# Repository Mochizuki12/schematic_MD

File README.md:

# schematic_MD
### 2chモータドライバのプロトタイプ<br>
[回路の仕様](https://github.com/Mochizuki12/schematic_MD/blob/v0.1.0/documents/MDdocument.pdf)<br>
[回路図](https://github.com/Mochizuki12/schematic_MD/blob/v0.1.0/documents/MD_schematics.pdf)<br>
[PCB](https://github.com/Mochizuki12/schematic_MD/blob/v0.1.0/documents/pcb.pdf)<br>

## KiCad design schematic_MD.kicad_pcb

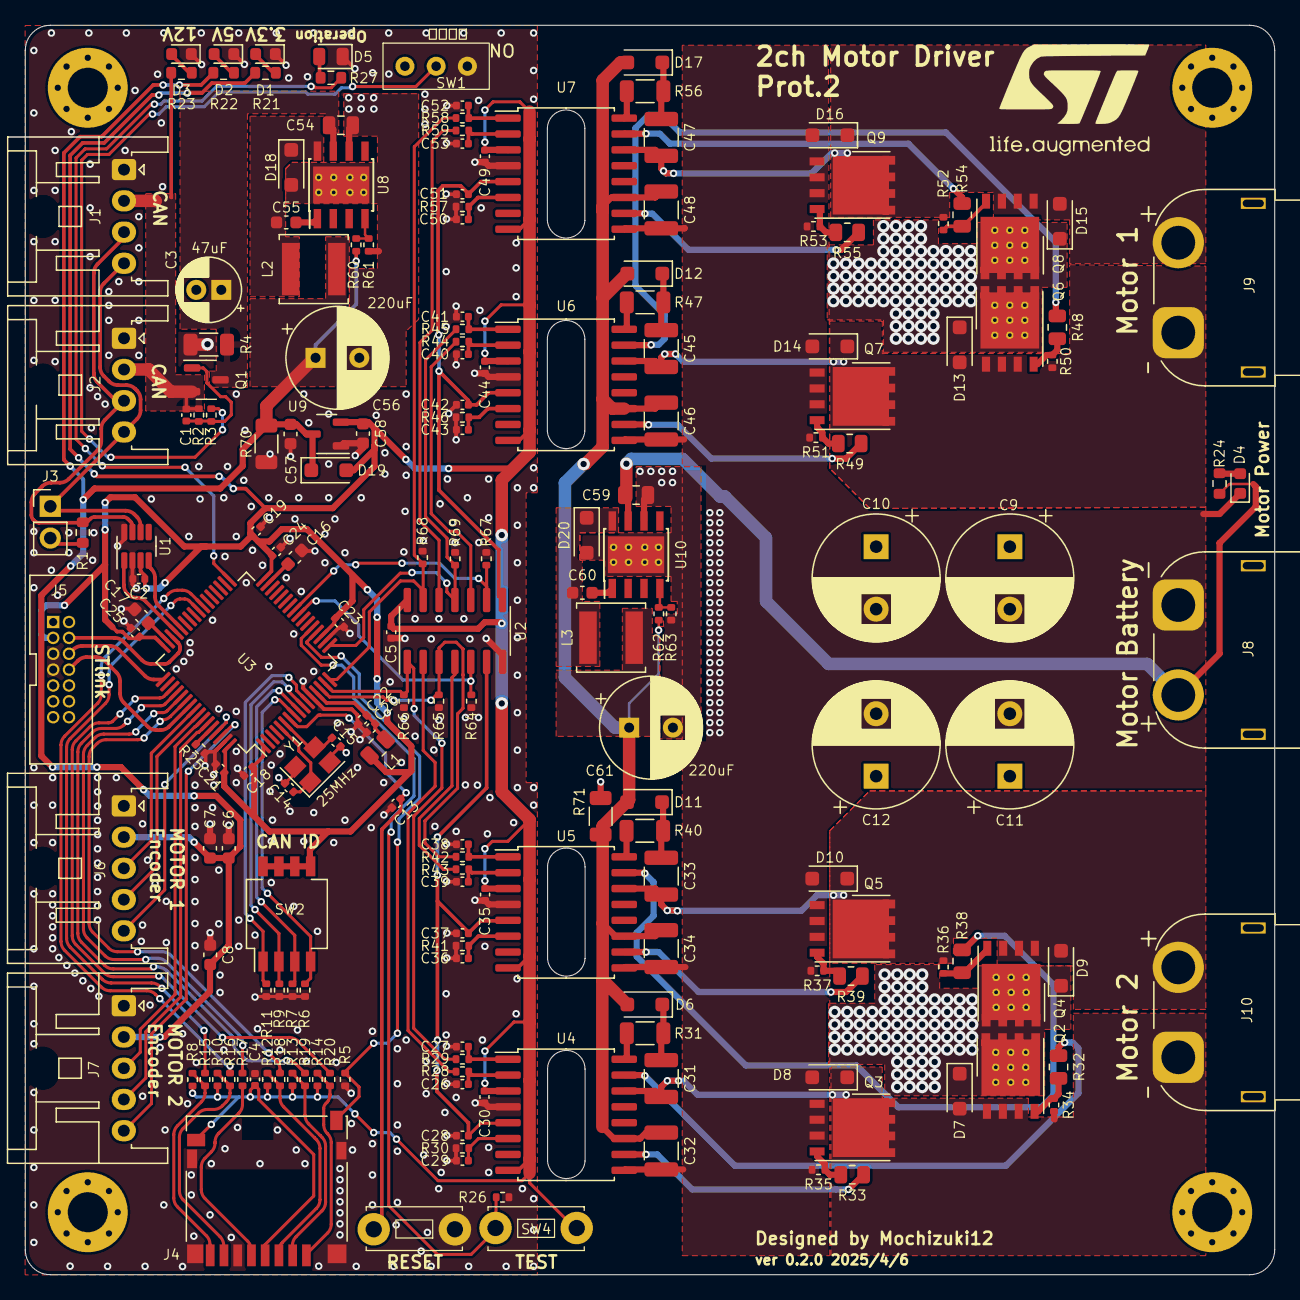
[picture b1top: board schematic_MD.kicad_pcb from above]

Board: 2 copper layers, 100.0 x 100.0 mm, 193 parts (0 on the bottom side), 113 nets.

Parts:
C1, C2, C4, C5, C13, C18, C21, C22, C23, C24, C25, C28, C29, C30, C35, C36, C37, C42, C43, C44, C49, C50, C51: 0.1uF; C_0402_1005Metric
C3: 47uF; CP_Radial_D5.0mm_P2.00mm
C6, C57, C58: 1uF; C_0603_1608Metric
C7, C8: 0.1uF; C_0603_1608Metric
C9, C10, C11, C12: 330uF; CP_Radial_D10.0mm_P5.00mm
C14, C15: 18pF; C_0402_1005Metric
C16, C17: 2.2uF; C_0603_1608Metric
C19: 4.7uF; C_0402_1005Metric
C20: 1uF; C_0402_1005Metric
C26, C27, C38, C39, C40, C41, C52, C53: 33pF; C_0402_1005Metric
C31, C32, C33, C34, C45, C46, C47, C48: 10uF; C_1210_3225Metric
C54, C59: 10uF; C_0805_2012Metric
C55, C60: 0.01uF; C_0603_1608Metric
C56, C61: 220uF; CP_Radial_D8.0mm_P3.50mm
D1, D2, D3, D4: LED; LED_0603_1608Metric
D5: LED; LED_0805_2012Metric
D6, D7, D8, D9, D10, D11, D12, D13, D14, D15, D16, D17, D18, D19, D20: D_Schottky; D_SOD-123F
H1, H2, H3, H4: MountingHole_Pad; MountingHole_3.2mm_M3_Pad_Via
J1, J2: CAN_Bus; JST_XA_S04B-XASK-1_1x04_P2.50mm_Horizontal
J3: Conn_02x01; PinHeader_1x02_P2.54mm_Vertical
J4: Micro_SD_Card_Det_Hirose_DM3AT; microSD_HC_Hirose_DM3D-SF
J5: Conn_02x07_Odd_Even; JTAG_box_connector
J6: Rotaly_encoder_1; JST_XA_S05B-XASK-1_1x05_P2.50mm_Horizontal
J7: Rotaly_encoder_2; JST_XA_S05B-XASK-1_1x05_P2.50mm_Horizontal
J8: XT60; AMASS_XT60PW-M_1x02_P7.20mm_Horizontal
J9, J10: XT60; AMASS_XT60PW-F_1x02_P7.20mm_Horizontal
L1: 600@100MHz; R_0805_2012Metric
L2, L3: 15uH; L_Sunlord_SWPA5040S
Q1: Q_PMOS_GSD; SOT-23-3
Q2, Q4, Q6, Q8: SQJ886EP-T1_GE3; Infineon_PG-TDSON-8_6.15x5.15mm_thermalvia
Q3, Q5, Q7, Q9: SQJ886EP-T1_GE3; Infineon_PG-TDSON-8_6.15x5.15mm
R1: 120; R_0603_1608Metric
R2, R3, R5, R6, R7, R8, R9, R10, R11, R12, R13, R14, R25, R26, R64, R65, R66, R67, R68, R69: 10k; R_0402_1005Metric
R4, R70, R71: 10k; R_1206_3216Metric
R15, R16, R17, R18, R19, R20: 0; R_0402_1005Metric
R21, R27: 330; R_0603_1608Metric
R22: 680; R_0603_1608Metric
R23: 2k; R_0603_1608Metric
R24: 3.6k; R_0603_1608Metric
R28, R29, R42, R43, R44, R45, R58, R59: 51; R_0402_1005Metric
R30, R34, R35, R36, R37, R41, R46, R50, R51, R52, R53, R57: 20k; R_0402_1005Metric
R31, R40, R47, R56: 0.1; R_1206_3216Metric
R32, R33, R38, R39, R48, R49, R54, R55: 10; R_0805_2012Metric
R60: 12k; R_0402_1005Metric
R61: 3.9k; R_0402_1005Metric
R62: 18k; R_0402_1005Metric
R63: 2k; R_0402_1005Metric
SW1: SW_SPDT; SS-12D
SW2: SW_DIP_x04; SW_DIP_SPSTx04_Slide_Copal_CHS-04B_W7.62mm_P1.27mm
SW3, SW4: SW_Push; TVBP06-B043
U1: MAX3051; SOT-23-8
U2: 74HC04; SOIC-14_3.9x8.7mm_P1.27mm
U3: STM32F405RGTx; LQFP-64_10x10mm_P0.5mm
U4, U5, U6, U7: UCC21520DW; SOIC-16W_7.5x10.3mm_P1.27mm
U8, U10: TPS5430DDA; TI_SO-PowerPAD-8_ThermalVias
U9: XC6206P332MR-G; SOT-23-3
Y1: 25MHz; Crystal_SMD_3225-4Pin_3.2x2.5mm

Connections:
+3.3V: C2.1, C4.2, C5.1, C18.1, C19.1, C21.1, C23.1, C24.1, C25.1, C30.1, C35.1, C44.1, C49.1, C58.1, D19.2 (A), J4.4 (VDD), J4.9 (DET_B), J5.3, L1.1, R8.1, R10.1, R12.1, R13.1, R14.1, R21.1, SW2.5, SW2.6, SW2.7, SW2.8, SW4.2, U1.3 (VDD), U2.14 (VCC), U3.1 (VBAT), U3.19 (VDD), U3.32 (VDD), U3.48 (VDD), U3.64 (VDD), U4.3 (VCCI), U4.8 (VCCI), U5.3 (VCCI), U5.8 (VCCI), U6.3 (VCCI), U6.8 (VCCI), U7.3 (VCCI), U7.8 (VCCI), U9.2 (VO)
+5V: C6.2, C7.2, C8.2, C56.1, C57.1, D19.1 (K), J6.2, J7.2, L2.2, R22.1, R60.1, R70.1, U9.3 (VI)
+12V: C1.1, J1.2, J2.2, Q1.2 (S), R2.1, R23.1
/Driver1/EN_left: C42.1, C51.1, U2.8, U6.5 (DIS), U7.5 (DIS)
/Driver1/H-bridge_left: C45.2, D13.2 (A), D14.1 (K), J9.1, Q6.1 (S), Q6.2 (S), Q6.3 (S), Q7.5 (D), R50.2, U6.14 (VSSA)
/Driver1/H-bridge_right: C47.2, D15.2 (A), D16.1 (K), J9.2, Q8.1 (S), Q8.2 (S), Q8.3 (S), Q9.5 (D), R52.2, U7.14 (VSSA)
/Driver1/Left_Highside_PWM_IN: R45.1, R69.1, U2.11, U3.17 (PA3)
/Driver1/Left_Lowside_PWM_IN: R44.1, U2.10
/Driver1/Right_Highside_PWM_IN: R58.1, R68.1, U2.13, U3.16 (PA2)
/Driver1/Right_Lowside_PWM_IN: R59.1, U2.12
/Driver/EN_left: C28.1, C37.1, U2.6, U4.5 (DIS), U5.5 (DIS)
/Driver/H-bridge_left: C31.2, D7.2 (A), D8.1 (K), J10.1, Q2.1 (S), Q2.2 (S), Q2.3 (S), Q3.5 (D), R34.2, U4.14 (VSSA)
/Driver/H-bridge_right: C33.2, D9.2 (A), D10.1 (K), J10.2, Q4.1 (S), Q4.2 (S), Q4.3 (S), Q5.5 (D), R36.2, U5.14 (VSSA)
/Driver/Left_Highside_PWM_IN: R29.1, R66.1, U2.1, U3.15 (PA1)
/Driver/Left_Lowside_PWM_IN: R28.1, U2.2
/Driver/Right_Highside_PWM_IN: R42.1, R65.1, U2.3, U3.14 (PA0)
/Driver/Right_Lowside_PWM_IN: R43.1, U2.4
/Logic_power/Power_IN: C3.1, C54.1, Q1.3 (D), R4.1, U8.7 (VIN)
/STM32F405/CAN_ID1: R11.1, SW2.1, U3.11 (PC3)
/STM32F405/CAN_ID2: R9.1, SW2.2, U3.10 (PC2)
/STM32F405/CAN_ID3: R7.1, SW2.3, U3.9 (PC1)
/STM32F405/CAN_ID4: R6.1, SW2.4, U3.8 (PC0)
/STM32F405/CAN_RX: U1.4 (RXD), U3.44 (PA11)
/STM32F405/CAN_TX: U1.1 (TXD), U3.45 (PA12)
/STM32F405/D0: R16.1, U3.39 (PC8)
/STM32F405/D1: R15.1, U3.40 (PC9)
/STM32F405/D2: R20.1, U3.51 (PC10)
/STM32F405/D3: R19.1, U3.52 (PC11)
/STM32F405/ENABLE_1: R64.1, U2.5, U3.24 (PC4)
/STM32F405/ENABLE_2: R67.1, U2.9, U3.25 (PC5)
/STM32F405/Motor1_A: J6.3, U3.56 (PB4)
/STM32F405/Motor1_B: J6.4, U3.57 (PB5)
/STM32F405/Motor1_Z: J6.5, U3.61 (PB8)
/STM32F405/Motor2_A: J7.3, U3.58 (PB6)
/STM32F405/Motor2_B: J7.4, U3.59 (PB7)
/STM32F405/Motor2_Z: J7.5, U3.62 (PB9)
/STM32F405/NRST: C13.1, SW3.2, U3.7 (NRST)
/STM32F405/SDCLK: R17.1, U3.53 (PC12)
/STM32F405/SDCMD: R18.1, U3.54 (PD2)
/STM32F405/SWCLK: J5.6, U3.49 (PA14)
/STM32F405/SWDIO: J5.4, U3.46 (PA13)
/STM32F405/SWO: J5.8, U3.55 (PB3)
GND1: C2.2, C3.2, C4.1, C5.2, C6.1, C7.1, C8.1, C13.2, C14.2, C15.2, C16.2, C17.2, C18.2, C19.2, C20.2, C21.2, C22.2, C23.2, C24.2, C25.2, C26.2, C27.2, C28.2, C29.2, C30.2, C35.2, C36.2, C37.2, C38.2, C39.2, C40.2, C41.2, C42.2, C43.2, C44.2, C49.2, C50.2, C51.2, C52.2, C53.2, C54.2, C56.2, C57.2, C58.2, D1.1 (K), D2.1 (K), D3.1 (K), D5.1 (K), D18.2 (A), J1.1, J2.1, J4.6 (VSS), J4.11 (SHIELD), J5.5, J5.7, J6.1, J7.1, R4.2, R5.2, R6.2, R7.2, R9.2, R11.2, R25.2, R26.2, R30.2, R41.2, R46.2, R57.2, R61.2, R64.2, R65.2, R66.2, R67.2, R68.2, R69.2, R70.2, SW1.3 (C), SW3.1, U1.2 (GND), U1.8 (RS), U2.7 (GND), U3.12 (VSSA), U3.18 (VSS), U3.63 (VSS), U4.4 (GND), U5.4 (GND), U6.4 (GND), U7.4 (GND), U8.6 (GND), U8.9 (GNDPAD), U9.1 (GND), Y1.2, Y1.4
GND2: C9.2, C10.2, C11.2, C12.2, C32.2, C34.2, C46.2, C48.2, C59.2, C61.2, D4.1 (K), D8.2 (A), D10.2 (A), D14.2 (A), D16.2 (A), D20.2 (A), J8.1, Q3.1 (S), Q3.2 (S), Q3.3 (S), Q5.1 (S), Q5.2 (S), Q5.3 (S), Q7.1 (S), Q7.2 (S), Q7.3 (S), Q9.1 (S), Q9.2 (S), Q9.3 (S), R35.2, R37.2, R51.2, R53.2, R63.2, R71.2, U4.9 (VSSB), U5.9 (VSSB), U6.9 (VSSB), U7.9 (VSSB), U10.6 (GND), U10.9 (GNDPAD)
Gate_power: C32.1, C34.1, C46.1, C48.1, C61.1, D6.2 (A), D11.2 (A), D12.2 (A), D17.2 (A), L3.2, R62.1, R71.1, U4.11 (VDDB), U5.11 (VDDB), U6.11 (VDDB), U7.11 (VDDB)
unnamed: D1.2 (A), R21.2
unnamed: D2.2 (A), R22.2
unnamed: D3.2 (A), R23.2
unnamed: D4.2 (A), R24.2
unnamed: D5.2 (A), R27.2
unnamed: C31.1, D6.1 (K), R31.2
unnamed: C33.1, D11.1 (K), R40.2
unnamed: C45.1, D12.1 (K), R47.2
unnamed: C47.1, D17.1 (K), R56.2
unnamed: C55.2, D18.1 (K), L2.1, U8.8 (PH)
unnamed: C60.2, D20.1 (K), L3.1, U10.8 (PH)
unnamed: J1.3, J2.3, R1.2, U1.7 (CANH)
unnamed: J1.4, J2.4, J3.1, U1.6 (CANL)
unnamed: J3.2, R1.1
unnamed: J4.5 (CLK), R17.2
unnamed: J4.3 (CMD), R12.2, R18.2
unnamed: J4.7 (DAT0), R10.2, R16.2
unnamed: J4.8 (DAT1), R8.2, R15.2
unnamed: J4.1 (DAT2), R14.2, R20.2
unnamed: J4.2 (DAT3/CD), R13.2, R19.2
unnamed: C1.2, Q1.1 (G), R2.2, R3.1
unnamed: Q2.4 (G), R32.2, R34.1
unnamed: Q3.4 (G), R33.2, R35.1
unnamed: Q4.4 (G), R36.1, R38.2
unnamed: Q5.4 (G), R37.1, R39.2
unnamed: Q6.4 (G), R48.2, R50.1
unnamed: Q7.4 (G), R49.2, R51.1
unnamed: Q8.4 (G), R52.1, R54.2
unnamed: Q9.4 (G), R53.1, R55.2
unnamed: R3.2, SW1.2 (B)
unnamed: R25.1, U3.60 (BOOT0)
unnamed: R26.1, SW4.1, U3.21 (PA5)
unnamed: R27.1, U3.33 (PB12)
unnamed: C14.1, U3.5 (PH0), Y1.1
unnamed: C15.1, U3.6 (PH1), Y1.3
unnamed: C16.1, U3.31 (VCAP_1)
unnamed: C17.1, U3.47 (VCAP_2)
unnamed: C29.1, R30.1, U4.6 (DT)
unnamed: C27.1, R29.2, U4.1 (INA)
unnamed: C26.1, R28.2, U4.2 (INB)
unnamed: R32.1, U4.15 (OUTA)
unnamed: R33.1, U4.10 (OUTB)
unnamed: R31.1, U4.16 (VDDA)
unnamed: C36.1, R41.1, U5.6 (DT)
unnamed: C38.1, R42.2, U5.1 (INA)
unnamed: C39.1, R43.2, U5.2 (INB)
unnamed: R38.1, U5.15 (OUTA)
unnamed: R39.1, U5.10 (OUTB)
unnamed: R40.1, U5.16 (VDDA)
unnamed: C43.1, R46.1, U6.6 (DT)
unnamed: C41.1, R45.2, U6.1 (INA)
unnamed: C40.1, R44.2, U6.2 (INB)
unnamed: R48.1, U6.15 (OUTA)
unnamed: R49.1, U6.10 (OUTB)
unnamed: R47.1, U6.16 (VDDA)
unnamed: C50.1, R57.1, U7.6 (DT)
unnamed: C52.1, R58.2, U7.1 (INA)
unnamed: C53.1, R59.2, U7.2 (INB)
unnamed: R54.1, U7.15 (OUTA)
unnamed: R55.1, U7.10 (OUTB)
unnamed: R56.1, U7.16 (VDDA)
unnamed: C55.1, U8.1 (BOOT)
unnamed: R60.2, R61.1, U8.4 (VSENSE)
unnamed: C60.1, U10.1 (BOOT)
unnamed: R62.2, R63.1, U10.4 (VSENSE)
SD_Detect: J4.10 (DET_A), R5.1, U3.20 (PA4)
VDDA: C20.1, C22.1, L1.2, U3.13 (VDDA)
Vdrive: C9.1, C10.1, C11.1, C12.1, C59.1, D7.1 (K), D9.1 (K), D13.1 (K), D15.1 (K), J8.2, Q2.5 (D), Q4.5 (D), Q6.5 (D), Q8.5 (D), R24.1, U10.7 (VIN)

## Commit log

2024-09-23 schematic update
2024-09-25 update Driver circuit
2024-09-27 update parts list
2024-09-27 add footprint
2024-09-28 pattern update
2024-10-01 Update motor driver circuit
2024-10-01 Change gate driver
2024-10-02 fix design
2024-10-03 add MOSFET pulldown
2024-10-05 fix powerline
2024-10-06 power line fix
2024-10-08 fix drive circuit
2024-10-08 add logic parts
2024-10-09 update pcb
2024-10-09 fix logic
2024-10-11 logic design update
2024-10-11 precompleate PCB design
2024-10-11 add gatedriver power
2024-10-12 add silkprint & GND plane
2024-10-12 add via
2024-10-14 release prot.1 v0.1.0
2024-11-06 add document
2024-11-08 add documents
2025-02-12 add branch v0.2.0
2025-02-22 Update PCB design & add microSD connector
2025-02-25 add SEPIC IC symbol
2025-02-28 wiring fix
2025-03-06 minor change
2025-03-07 change logic DCDC
2025-03-11 制御回路完成
2025-03-14 wired gate power
2025-03-18 pre compleate
2025-03-31 DCDCコンバータ部分を修正
2025-04-04 DRC 完了
2025-04-07 minor fix
2025-04-10 Modified DCDC converter coil
2025-04-10 Change GND plene
2025-04-14 update BOM
2025-04-14 Board for ordering
